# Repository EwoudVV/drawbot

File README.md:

## Drawbot

### Design: https://www.tinkercad.com/things/kSLyTMIcY53-drawbot

 - Made for [Hack Club Highway](https://highway.hackclub.com/)
 - This project is a 0.5 meter square drawing machine that I designed to be as fast and cheap as possible.
 - I made this project because I wanted to learn more about designing and using mechanisms, like the CoreXY belt design I used and the scotch-yoke mechanism used to lift the pen. I also wanted something functional, that I would use.

### Pictures

### Bill Of Materials

|Part                       |Qty|Price                    |Desc                                                   |Notes                                                                                 |Link                                                                                     |
|---------------------------|---|-------------------------|-------------------------------------------------------|--------------------------------------------------------------------------------------|-----------------------------------------------------------------------------------------|
|Arduino                    |1  |$29.30                   |Uno R3                                                 |not going to buy                                                                      |http://store.arduino.cc/collections/boards-modules/products/arduino-uno-rev3             |
|Pen                        |60 |$7.99                    |Bic Round Stic                                         |not going to buy                                                                      |https://us.bic.com/en_us/bic-round-stic-xtra-life-ball-point-pen-black-60-pack.html      |
|500mm Aluminium Extrusion  |4  |$25.99                   |500m V-slot aluminum extrusions                        |They come with extra accessories like connectors                                      |https://www.amazon.com/Seekliny-Aluminum-Extrusion-V-Slotted-Accessories/dp/B0DY7FKXZ9/  |
|Linear Motion Rod Shaft    |2  |$29.99                   |Linear shaft for the toolhead to move on               |Comes with bearings for the toolhead                                                  |https://www.amazon.com/uxcell-Bearing-Support-Automated-Machines/dp/B0CK4Z3M15           |
|Stepper Motor Nema 17      |2  |$25.99                   |Motors to drive the gantry                             |High torque and high speed                                                            |https://www.amazon.com/Stepper-Motor-Bipolar-64oz-Printer/dp/B00PNEQI7W                  |
|Timing Belt                |1  |$14.99                   |5m belt                                                |Extra accessories included like driver and idler wheels and belt clamps and tensioners|https://www.amazon.com/KeeYees-Timing-Tensioner-Torsion-Printer/dp/B07JKT5BZQ            |
|Stepper Motor Driver Module|2  |$7.59                    |Stepper motor drivers                                  |                                                                                      |https://www.amazon.com/Stepper-Printer-StepStick-Envistia-Mall/dp/B07QT7N3T2             |
|Servo                      |1  |$2.99                    |Fast servo that has metal gears and is small           |                                                                                      |https://speedyfpv.com/products/mg90d-metal-digital-servo-new?variant=45194443030742      |
|Limit switches             |2  |$5.56                    |SS-5GL02                                               |For homing the toolhead                                                               |https://www.digikey.com/en/products/detail/omron-electronics-inc-emc-div/SS-5GL02/3102937|
|Roller plate               |2  |$11.97                   |Roller plates for attachment on the aluminum extrusions|Adjustable                                                                            |https://www.amazon.com/QWORK-V-Wheel-Aluminum-Profile-Printer/dp/B0CHRYLV1V              |
|Belt idler wheels          |5  |$7.99                    |Idler wheels for when the belt turns                   |4 extra are needed                                                                    |https://www.amazon.com/Timing-Belt-Idler-Pulley-Printer/dp/B0BSPCHTD3                    |
|                           |   |SUBTOTAL: $133.06        |no extras                                              |                                                                                      |                                                                                         |
|                           |   |TOTAL: $141.38           |no extras and tax                                      |assumes MA sales tax                                                                  |                                                                                         |
|                           |   |GRAND TOTAL: $170.35      |extras                                                 |                                                                                      |                                                                                         |
|                           |   |GRAND GRAND TOTAL: $181.00|extras and tax                                         |assumes MA sales tax                                                                  |                                                                                         |

### Alternate BOM

|Part                       |Qty|Price           |Desc                                                   |Notes                                                                                 |Link                                                                                                                                                                                                                                                                                                                                                                                                                                                                                                                                                                                                                                                                                                                                                                                                                                                                      |
|---------------------------|---|----------------|-------------------------------------------------------|--------------------------------------------------------------------------------------|--------------------------------------------------------------------------------------------------------------------------------------------------------------------------------------------------------------------------------------------------------------------------------------------------------------------------------------------------------------------------------------------------------------------------------------------------------------------------------------------------------------------------------------------------------------------------------------------------------------------------------------------------------------------------------------------------------------------------------------------------------------------------------------------------------------------------------------------------------------------------|
|Arduino                    |1  |$29.30          |Uno R3                                                 |not going to buy                                                                      |                                                                                                                                                                                                                                                                                                                                                                                                                                                                                                                                                                                                                                                                                                                                                                                                                                                                          |
|Pen                        |60 |$7.99           |Bic Round Stic                                         |not going to buy                                                                      |                                                                                                                                                                                                                                                                                                                                                                                                                                                                                                                                                                                                                                                                                                                                                                                                                                                                          |
|500mm Aluminium Extrusion  |4  |$25.99          |500m V-slot aluminum extrusions                        |They come with extra accessories like connectors                                      |https://www.aliexpress.us/item/3256804642902887.html?src=google&pdp_npi=4%40dis%21USD%217.62%214.95%21%21%21%21%21%40%2112000046464978432%21ppc%21%21%21&src=google&albch=shopping&acnt=615-992-9880&isdl=y&slnk=&plac=&mtctp=&albbt=Google_7_shopping&aff_platform=google&aff_short_key=_oFgTQeV&gclsrc=aw.ds&albagn=888888&ds_e_adid=&ds_e_matchtype=&ds_e_device=c&ds_e_network=x&ds_e_product_group_id=&ds_e_product_id=en3256804642902887&ds_e_product_merchant_id=106987257&ds_e_product_country=US&ds_e_product_language=en&ds_e_product_channel=online&ds_e_product_store_id=&ds_url_v=2&albcp=22525427924&albag=&isSmbAutoCall=false&needSmbHouyi=false&gad_source=1&gad_campaignid=22518985128&gbraid=0AAAAA_TvRHohDlpwH1t31wwRTStl9wvTn&gclid=CjwKCAjw7rbEBhB5EiwA1V49nQ8Jo3CpTYPn01uYwYKQ9a22NtzzU9K2DkHqgGaVjLixHldWkVV13xoCB6wQAvD_BwE&gatewayAdapt=glo2usa |
|Linear Motion Rod Shaft    |2  |$17.64          |Linear shaft for the toolhead to move on               |                                                                                      |https://www.aliexpress.us/item/2255800403003227.html?src=google&pdp_npi=4%40dis%21USD%215.10%215.10%21%21%21%21%21%40%2110000003452701986%21ppc%21%21%21&src=google&albch=shopping&acnt=708-803-3821&isdl=y&slnk=&plac=&mtctp=&albbt=Google_7_shopping&aff_platform=google&aff_short_key=UneMJZVf&gclsrc=aw.ds&albagn=888888&ds_e_adid=&ds_e_matchtype=&ds_e_device=c&ds_e_network=x&ds_e_product_group_id=&ds_e_product_id=en2255800403003227&ds_e_product_merchant_id=5544025252&ds_e_product_country=US&ds_e_product_language=en&ds_e_product_channel=online&ds_e_product_store_id=&ds_url_v=2&albcp=19413040701&albag=&isSmbAutoCall=false&needSmbHouyi=false&gad_source=1&gad_campaignid=19420347529&gbraid=0AAAAAD6I-hF0245CxOJHj-UJ7bSmDm36F&gclid=CjwKCAjw7rbEBhB5EiwA1V49nZwHaAKpbgu1fPc7DIDs8G7P-iGvrT7iIwYScHBpzhI0BMiAgKYHURoCq9gQAvD_BwE&gatewayAdapt=glo2usa|
|Linear motion rod clamp    |4  |$17.1           |                                                       |                                                                                      |https://www.aliexpress.us/item/2255799899348947.html?gatewayAdapt=glo2usa4itemAdapt                                                                                                                                                                                                                                                                                                                                                                                                                                                                                                                                                                                                                                                                                                                                                                                       |
|Linear bearings            |2  |$13.27          |                                                       |                                                                                      |https://www.aliexpress.us/item/2251832487047487.html?spm=a2g0o.productlist.main.3.54df26fc2UpYiK&algo_pvid=85eeae5b-9a15-44c1-90ea-e4faa7d98317&algo_exp_id=85eeae5b-9a15-44c1-90ea-e4faa7d98317-2&pdp_ext_f=%7B%22order%22%3A%22153%22%2C%22eval%22%3A%221%22%7D&pdp_npi=4%40dis%21USD%2117.69%2113.27%21%21%2117.69%2113.27%21%402103201917541703882386169ef02f%2164097981491%21sea%21US%210%21ABX&curPageLogUid=IfCRcKenJCX7&utparam-url=scene%3Asearch%7Cquery_from%3A&_gl=1*1ko6jw4*_gcl_au*MTk4NzE3NjcwLjE3NTQxNzAzODU.*_ga*MzY4MzUwNzkzMTI2MDkxLjE3NDc2MDY2MDg3Njc.*_ga_VED1YSGNC7*czE3NTQxNzAzODQkbzEkZzEkdDE3NTQxNzAzODkkajU1JGwwJGgw                                                                                                                                                                                                                            |
|Stepper Motor Nema 17      |2  |$15.22          |Motors to drive the gantry                             |High torque and high speed                                                            |https://www.aliexpress.us/item/2251832683239784.html?src=google&pdp_npi=4%40dis%21USD%214.45%213.78%21%21%21%21%21%40%2165443571322%21ppc%21%21%21&src=google&albch=shopping&acnt=708-803-3821&isdl=y&slnk=&plac=&mtctp=&albbt=Google_7_shopping&aff_platform=google&aff_short_key=UneMJZVf&gclsrc=aw.ds&albagn=888888&ds_e_adid=&ds_e_matchtype=&ds_e_device=c&ds_e_network=x&ds_e_product_group_id=&ds_e_product_id=en2251832683239784&ds_e_product_merchant_id=100982560&ds_e_product_country=US&ds_e_product_language=en&ds_e_product_channel=online&ds_e_product_store_id=&ds_url_v=2&albcp=19108228023&albag=&isSmbAutoCall=false&needSmbHouyi=false&gad_source=1&gad_campaignid=19108292148&gbraid=0AAAAAD6I-hEk8pbPKbQHAsRlzOuaOHWji&gclid=CjwKCAjw7rbEBhB5EiwA1V49nb6DJGdRqMjYuNWtBtJyw-fqecrs39E0UI3GKHXx1VbWHtdZy6qYcBoCQDYQAvD_BwE&gatewayAdapt=glo2usa       |
|Timing Belt                |1  |$9.35           |5m belt                                                |Extra accessories included like driver and idler wheels and belt clamps and tensioners|https://www.aliexpress.us/item/3256803959490903.html?gatewayAdapt=glo2usa4itemAdapt                                                                                                                                                                                                                                                                                                                                                                                                                                                                                                                                                                                                                                                                                                                                                                                       |
|Stepper Motor Driver Module|2  |$10.55          |Stepper motor drivers                                  |                                                                                      |https://www.aliexpress.us/item/2255800140733695.html?spm=a2g0o.productlist.main.8.608a64d6NGzeHa&algo_pvid=e55d2704-2785-4781-b016-b448045a97a3&algo_exp_id=e55d2704-2785-4781-b016-b448045a97a3-7&pdp_ext_f=%7B%22order%22%3A%2253%22%2C%22eval%22%3A%221%22%7D&pdp_npi=4%40dis%21USD%218.08%215.33%21%21%218.08%215.33%21%402101efeb17541709004351878e50a0%2110000001342223857%21sea%21US%210%21ABX&curPageLogUid=KiUrBYL8ZibD&utparam-url=scene%3Asearch%7Cquery_from%3A&_gl=1*15ltvc9*_gcl_au*MTk4NzE3NjcwLjE3NTQxNzAzODU.*_ga*MzY4MzUwNzkzMTI2MDkxLjE3NDc2MDY2MDg3Njc.*_ga_VED1YSGNC7*czE3NTQxNzAzODQkbzEkZzEkdDE3NTQxNzA5MDEkajYwJGwwJGgw                                                                                                                                                                                                                           |
|Servo                      |1  |$2.18           |Fast servo that has metal gears and is small           |                                                                                      |https://www.aliexpress.us/item/3256806338932286.html?gatewayAdapt=glo2usa4itemAdapt                                                                                                                                                                                                                                                                                                                                                                                                                                                                                                                                                                                                                                                                                                                                                                                       |
|Limit switches             |2  |$5.56           |SS-5GL02                                               |For homing the toolhead                                                               |https://www.digikey.com/en/products/detail/omron-electronics-inc-emc-div/SS-5GL02/3102937                                                                                                                                                                                                                                                                                                                                                                                                                                                                                                                                                                                                                                                                                                                                                                                 |
|Roller plate               |2  |$9              |Roller plates for attachment on the aluminum extrusions|NOT Adjustable                                                                        |https://www.aliexpress.us/item/3256806120290201.html?gatewayAdapt=glo2usa4itemAdapt                                                                                                                                                                                                                                                                                                                                                                                                                                                                                                                                                                                                                                                                                                                                                                                       |
|Belt idler wheels          |5  |$1.24           |Idler wheels for when the belt turns                   |4 extra are needed                                                                    |https://www.aliexpress.us/item/2251832631013486.html?gatewayAdapt=glo2usa4itemAdapt                                                                                                                                                                                                                                                                                                                                                                                                                                                                                                                                                                                                                                                                                                                                                                                       |
|                           |   |SUBTOTAL: $127.1|no extras                                              |                                                                                      |                                                                                                                                                                                                                                                                                                                                                                                                                                                                                                                                                                                                                                                                                                                                                                                                                                                                          |
|                           |   |TOTAL: $135.05  |no extras and tax                                      |assumes MA sales tax                                                                  |                                                                                                                                                                                                                                                                                                                                                                                                                                                                                                                                                                                                                                                                                                                                                                                                                                                                          |

### Software and documentation

 - The machine runs a custom Uno R4 WiFi + CNC Shield V3.00 firmware in [`code/drawbot_r4/`](code/drawbot_r4/) (compile, upload, and command docs in its README).
 - The machine is **commissioned and drawing**: scale verified, pen calibrated, and a 35-minute endurance run completed with zero errors. Because the bottom (Y-) limit switch is defective, the machine operates with **manual homing** (`M50 X0 Y0` after parking at the corner); `G28` will not complete until that switch is replaced.
 - Full operational history and debug findings live in [`docs/HANDOFF_V2.md`](docs/HANDOFF_V2.md) (supersedes [`docs/HANDOFF.md`](docs/HANDOFF.md)). Wiring and commissioning guides are in [`code/drawbot_r4/docs/`](code/drawbot_r4/docs/).
 - Presentation workflow: park at the corner, `M50 X0 Y0`, then `python3 code/drawbot_r4/tools/stream_gcode.py --ble code/drawbot_r4/examples/stress_30min.gcode`. Generate new hatch patterns with `tools/gen_stress_pattern.py --paper WxH`.

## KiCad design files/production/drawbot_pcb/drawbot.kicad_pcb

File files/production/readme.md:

Production files like print jobs go here

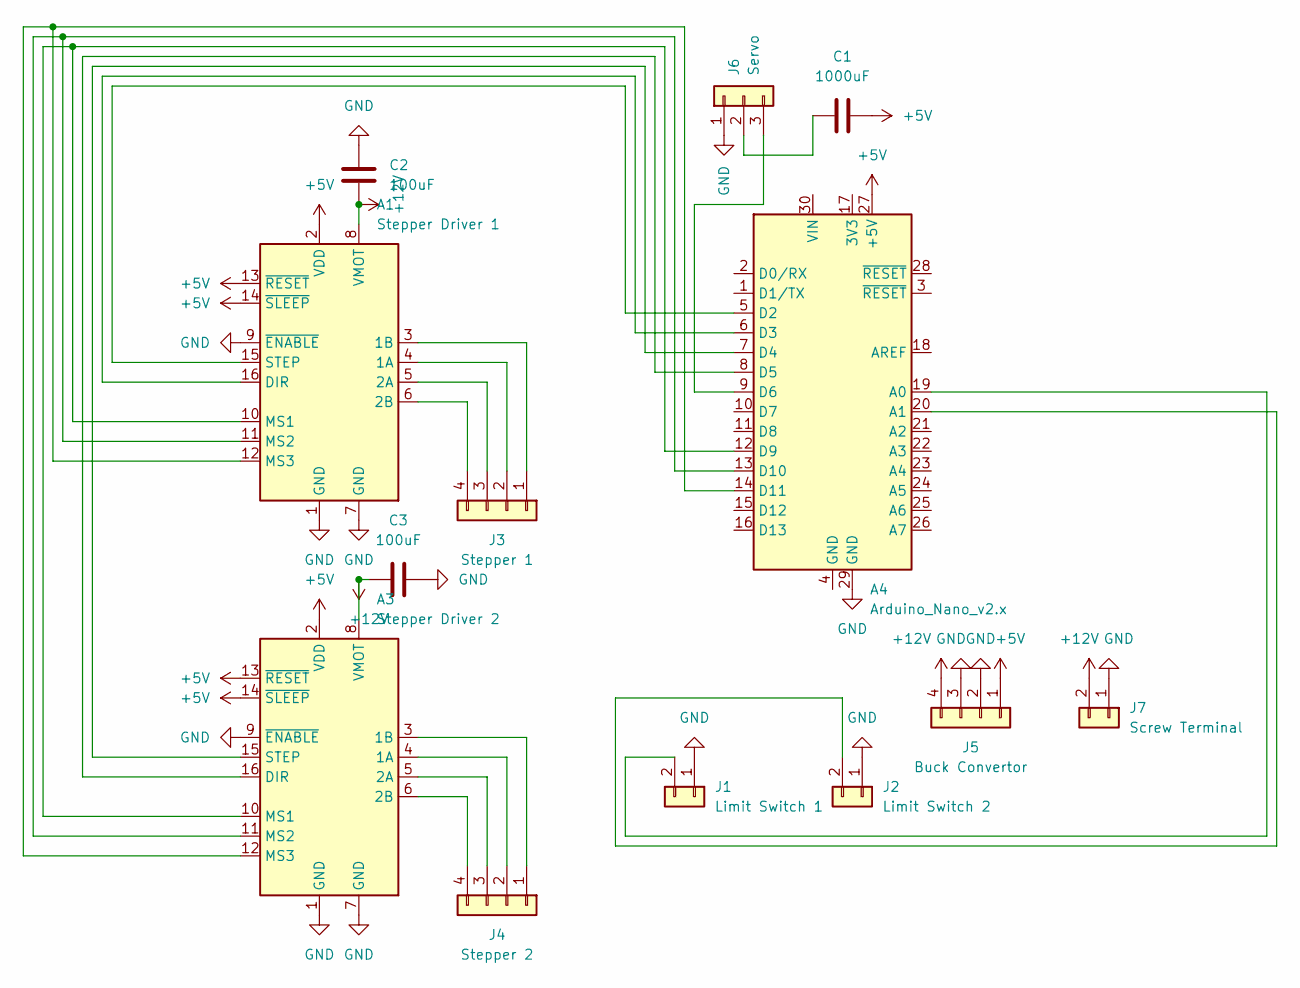
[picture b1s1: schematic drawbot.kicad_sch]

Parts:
A1: Stepper Driver 1; Pololu_Breakout-16_15.2x20.3mm
A3: Stepper Driver 2; Pololu_Breakout-16_15.2x20.3mm
A4: Arduino_Nano_v2.x; Arduino_Nano
C1: 1000uF; CP_Radial_D10.0mm_P5.00mm
C2, C3: 100uF; CP_Radial_D6.3mm_P2.50mm
J1: Limit Switch 1; PinHeader_1x02_P2.54mm_Vertical
J2: Limit Switch 2; PinHeader_1x02_P2.54mm_Vertical
J3: Stepper 1; PinHeader_1x04_P2.54mm_Vertical
J4: Stepper 2; PinHeader_1x04_P2.54mm_Vertical
J5: Buck Convertor; PinHeader_1x04_P2.54mm_Vertical
J6: Servo; PinHeader_1x03_P2.54mm_Vertical
J7: Screw Terminal; TerminalBlock_bornier-2_P5.08mm

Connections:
+5V: A1.2 (VDD), A1.13 (~RESET), A1.14 (~SLEEP), A3.2 (VDD), A3.13 (~RESET), A3.14 (~SLEEP), A4.27 (+5V), C1.1, J5.1
+12V: A1.8 (VMOT), A3.8 (VMOT), C2.2, C3.1, J5.4, J7.2
GND: A1.1 (GND), A1.7 (GND), A1.9 (~ENABLE), A3.1 (GND), A3.7 (GND), A3.9 (~ENABLE), A4.29 (GND), C2.1, C3.2, J1.1, J2.1, J5.2, J5.3, J6.1, J7.1
unnamed: A1.4 (1A), J3.2
unnamed: A1.3 (1B), J3.1
unnamed: A1.5 (2A), J3.3
unnamed: A1.6 (2B), J3.4
unnamed: A1.16 (DIR), A4.6 (D3)
unnamed: A1.10 (MS1), A3.10 (MS1), A4.12 (D9)
unnamed: A1.11 (MS2), A3.11 (MS2), A4.13 (D10)
unnamed: A1.12 (MS3), A3.12 (MS3), A4.14 (D11)
unnamed: A1.15 (STEP), A4.5 (D2)
unnamed: A3.4 (1A), J4.2
unnamed: A3.3 (1B), J4.1
unnamed: A3.5 (2A), J4.3
unnamed: A3.6 (2B), J4.4
unnamed: A3.16 (DIR), A4.8 (D5)
unnamed: A3.15 (STEP), A4.7 (D4)
unnamed: A4.19 (A0), J1.2
unnamed: A4.20 (A1), J2.2
unnamed: A4.9 (D6), J6.3
unnamed: C1.2, J6.2

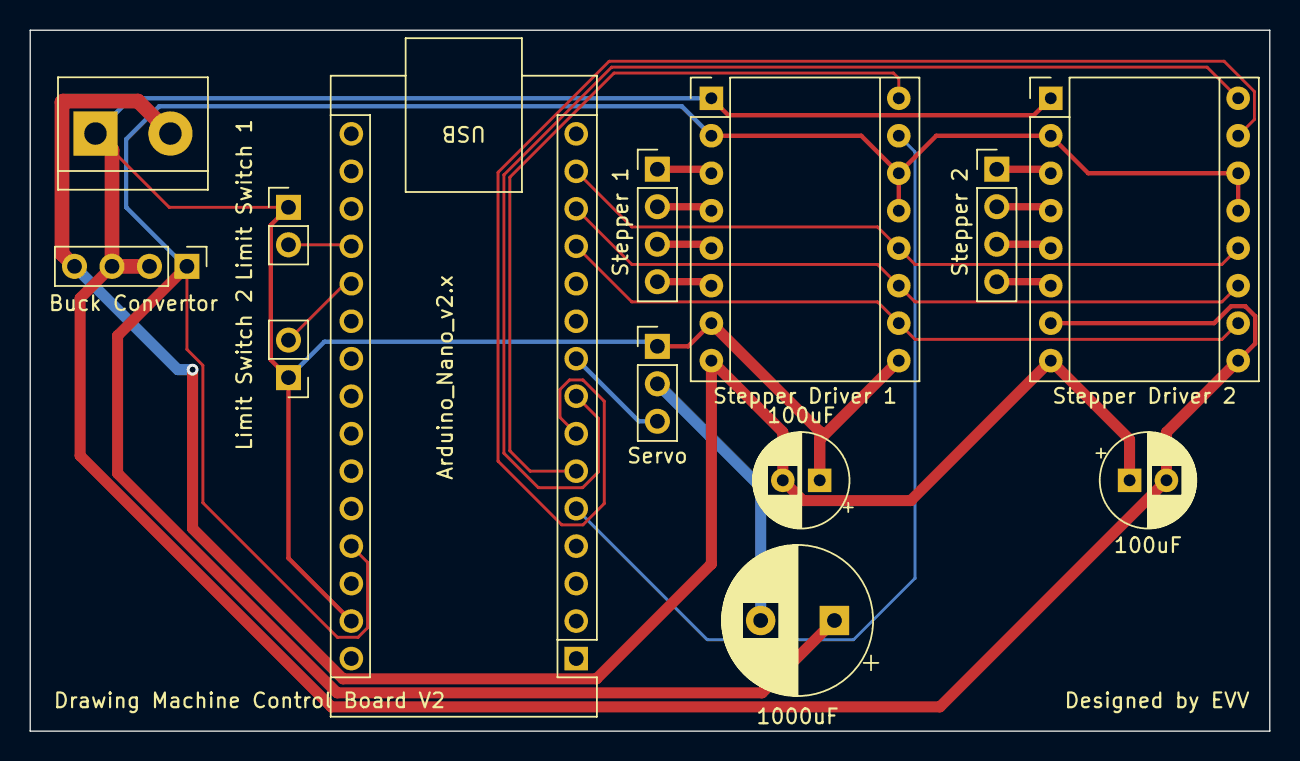
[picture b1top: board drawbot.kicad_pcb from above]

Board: 2 copper layers, 84.0 x 47.5 mm, 13 parts (0 on the bottom side), 22 nets.

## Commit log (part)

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2025-05-18 Create README.md
    eeee
2025-05-18 Create readme cad
2025-05-18 Create production md
2025-05-18 stuffff
2025-05-18 WHY DOES IT NEED TO BE A CSV
2025-05-18 stuffs
2025-05-24 Update journal.md (from yesterday)
2025-05-24 add stuff i was supposed to add
2025-05-24 found much cheaper items, total is $50 less :)
2025-05-24 move bom to main
2025-06-29 find cheaper servo
2025-07-23 Update bom.csv (added item, removed an item, recalculated costs, gremmer)
2025-07-25 Update journal.md (add total time)
2025-07-25 why do i need bom in root in csv ***and*** readme in markdown
2025-07-25 Update README.md (add design link)
2025-07-25 Create drawbot.ino (i forgor to add code ._.
2025-08-02 add step files for cad
2025-11-08 add new code
2026-02-04 upload updated cad, upoad code
    updated cad: top plate of toolhead
    code: arduino code recieving gcode from serial, python code sending gcode line by line.
    later: queue gcode, send in chunks for efficiency.
2026-02-04 add individual printed cad files
2026-02-04 Refine usage instructions and comments in stream_gcode.py
    Updated usage instructions and comments in stream_gcode.py.
2026-02-04 Refine comments in drawbot_homing.ino
    Updated comments for clarity and consistency throughout the code.
